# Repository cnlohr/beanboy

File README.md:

# beanboy

The beanboy is a handheld game system with 3 buttons, and an oled display.  It has the following specs:
 * Powered by a 9V Battery
 * 128x128 RB150-2828KSWKG01 SPI OLED display from Ronboe ($2.50)
 * 3 Silicone buttons with pressure sensitivity
 * TBD: Runtime
 * CH572 Main Processor
   * 240kB Flash
   * 12kB RAM
   * 60MHz
   * RISC-V rv32imbc processor
   * 2.4GHz iSLER radio comms

(Early drafts, not ready yet)

## Installation / getting started

Follow these instructions: [https://github.com/cnlohr/ch32fun/wiki](https://github.com/cnlohr/ch32fun/wiki)

## Graphics API

The bean boy uses a monochrome 128x128 display.

### Input

You get "pressures" for button 1, button 2, button 3, and the battery level. (For now, just print the values to the screen, we will be changing the levels)

```c
	uint32_t pressures[4];
	BeanBoyReadPressures( pressures );
```

### Sprites

Have .png files in `sprites/` folder, then on compile, they will turn into the object name itself, when you say `make clean firmware.elf`

```c
void RenderBSprite( const bsprite * spr, int outx, int outy );
```

For instance if you have `sprites/bubble.png`, you can call:

```c
	RenderBSprite( &bubble, x, y );
```

You can use purple or actual transparency to indicate transparent, then use white or black.

### Basic Drawing

Graphics APIs are from [the ch32v003 ssd1306 driver](https://github.com/cnlohr/ch32fun/blob/master/extralibs/ssd1306.h)

```c
#define SSD1306_W 128
#define SSD1306_H 128

void ssd1306_drawPixel(uint32_t x, uint32_t y, int color);
void ssd1306_xorPixel(uint32_t x, uint32_t y);
void ssd1306_drawImage(uint32_t x, uint32_t y, const unsigned char* input, uint32_t width, uint32_t height, uint32_t color_mode);
void ssd1306_drawFastVLine(int32_t x, int32_t y, int32_t h, uint32_t color);
void ssd1306_drawFastHLine(uint32_t x, uint32_t y, uint32_t w, uint32_t color);
void ssd1306_drawLine(int x0, int y0, int x1, int y1, uint32_t color);
void ssd1306_drawCircle(int x, int y, int radius, int color);
void ssd1306_fillCircle(int x, int y, int radius, int color);
void ssd1306_drawRect(int32_t x, int32_t y, uint32_t w, uint32_t h, uint32_t color);
void ssd1306_fillRect(uint32_t x, uint32_t y, uint8_t w, uint32_t h, uint32_t color);
void ssd1306_xorrect(uint8_t x, uint8_t y, uint8_t w, uint8_t h);
void ssd1306_drawchar(uint8_t x, uint8_t y, uint8_t chr, uint8_t color);
void ssd1306_drawstr(uint8_t x, uint8_t y, char *str, uint8_t color);
void ssd1306_drawchar_sz(uint8_t x, uint8_t y, uint8_t chr, uint8_t color, font_size_t font_size);
void ssd1306_drawstr_sz(uint8_t x, uint8_t y, char *str, uint8_t color, font_size_t font_size);
```

### Wireless API

```c
// call these
void ISLERSetup( int channel ); 
void ISLERSend( uint8_t message, int messageLength );

struct MyGameStruct
{
	uint32_t id;
	uint8_t something;
} __attribute__((packed));

void ISLERCallback( uint8_t * txmac, uint8_t * message, int messageLength, int rssi )
{
	struct MyGameStruct * st = (struct MyGameStruct*)message;

	if( messageLength < sizeof( struct MyGameStruct ) )
		return;

	printf( "%d\n", st->something );
}

void main()
{
	ISLERSetup( 9 );

	struct MyGameStruct st;
	st.id = 0x1234778a; // Some ID so you don't get confused with other BLE-messages.
	st.something = 5;

	ISLERSend( &st, sizeof( st ) );
}
```

## TODO

TODO:

1. ~~Build up two beanboys~~
2. ~~Check to see if the radio code works.~~
3. ~~Make sprite import code.~~
4. ~~Add transparency code.~~
5. ~~Add API for comms~~
6. Add networking to emu
7. Add button debouncing
8. Add compression to sprites
9. Add sprite rotation maybe?
10. Add sprite scaling maybe?
11. "Pass the puffer"  "Hot Potato with puffer fish"
  a. Choose between 2 and 6 players
  b. Randomly assign X amount of passes.
  c. number of passes remaining is unknown.
12. Shut the box.
  a. Rules too complicated for me to write here.

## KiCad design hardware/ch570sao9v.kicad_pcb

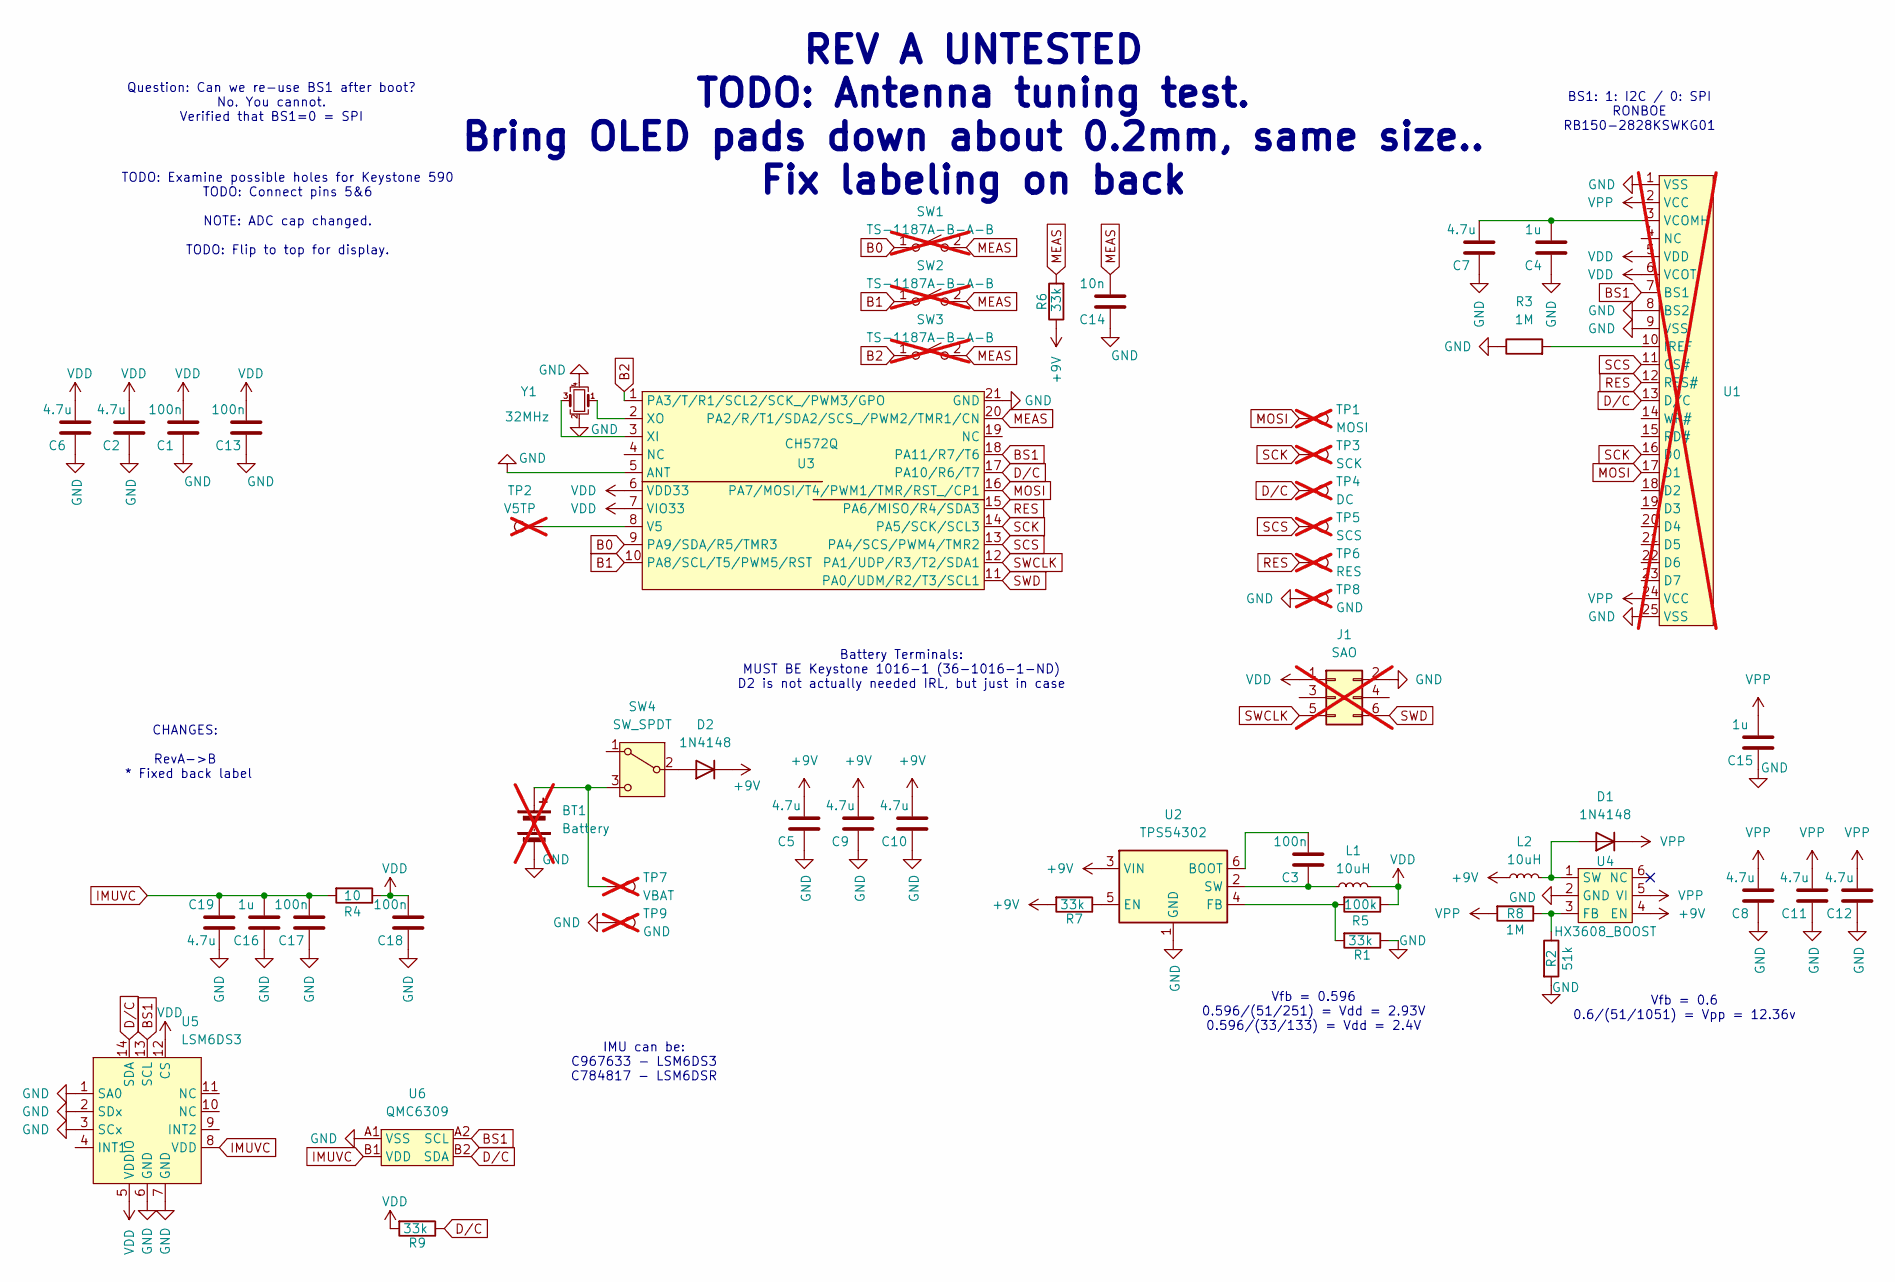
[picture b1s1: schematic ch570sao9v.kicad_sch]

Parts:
BT1: Battery; not fitted
C1, C3, C13, C17, C18: 100n; R_0402_1005Metric; LCSC C307331
C2, C5, C6, C7, C8, C9, C10, C11, C12, C19: 4.7u; C_1206_3216Metric; LCSC C29823
C4, C15, C16: 1u; R_0402_1005Metric; LCSC C52923
C14: 10n; R_0402_1005Metric; LCSC C15195
D1, D2: 1N4148; D_SOD-323; LCSC C2128
J1: SAO; PinHeader_2x03_P2.54mm_Vertical_SMD; not fitted
L1, L2: 10uH; L_1008_2520Metric; LCSC C37428
R1, R6, R7, R9: 33k; R_0402_1005Metric_COMPACT; LCSC C25779
R2: 51k; R_0402_1005Metric_COMPACT; LCSC C25794
R3, R8: 1M; R_0402_1005Metric_COMPACT; LCSC C26083
R4: 10; R_0402_1005Metric_COMPACT; LCSC C25077
R5: 100k; R_0402_1005Metric_COMPACT; LCSC C25741
SW1, SW2, SW3: TS-1187A-B-A-B; BTC007_Button_Silicone; not fitted
SW4: SW_SPDT; SW_SPDT_PCM12; LCSC C3008585
TP1: MOSI; TestPoint_Pad_D1.0mm; not fitted
TP2: V5TP; TestPoint_Pad_D1.0mm; not fitted
TP3: SCK; TestPoint_Pad_D1.0mm; not fitted
TP4: DC; TestPoint_Pad_D1.0mm; not fitted
TP5: SCS; TestPoint_Pad_D1.0mm; not fitted
TP6: RES; TestPoint_Pad_D1.0mm; not fitted
TP7: VBAT; TestPoint_Pad_D1.0mm; LCSC C6063943; not fitted
TP8: GND; TestPoint_Pad_D1.0mm; not fitted
TP9: GND; TestPoint_Pad_D1.0mm; LCSC C6063943; not fitted
U1: RB150-2828KSWKG01; not fitted
U2: TPS54302; SOT-23-6; LCSC C311983
U3: CH572Q; QFN-20-1EP_3x3mm_P0.4mm_EP1.65x1.65mm; LCSC C46597863
U4: HX3608_BOOST; SOT-23-6; LCSC C296278
U5: LSM6DS3; LGA-14_3x2.5mm_P0.5mm_LayoutBorder3x4y_EVEN_PADS; LCSC C784817
U6: QMC6309; WLP-4_0.83x0.83mm_P0.4mm; LCSC C5439871
Y1: 32MHz; Crystal_SMD_2016-4Pin_2.0x1.6mm; LCSC C37635323

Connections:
+9V: C5.1, C9.1, C10.1, D2.1 (K), L2.1, R6.1, R7.2, U2.3 (VIN), U4.4 (EN)
B0: SW1.1 (A), U3.9 (PA9/SDA/R5/TMR3)
B1: SW2.1 (A), U3.10 (PA8/SCL/T5/PWM5/RST)
B2: SW3.1 (A), U3.1 (PA3/T/R1/SCL2/SCK_/PWM3/GPO)
BS1: U1.7 (BS1), U3.18 (PA11/R7/T6), U5.13 (SCL), U6.A2 (SCL)
D/C: R9.1, TP4.1, U1.13 (D/C), U3.17 (PA10/R6/T7), U5.14 (SDA), U6.B2 (SDA)
GND: BT1.2 (-), C1.2, C2.2, C4.2, C5.2, C6.2, C7.2, C8.2, C9.2, C10.2, C11.2, C12.2, C13.2, C14.2, C15.2, C16.2, C17.2, C18.2, C19.1, J1.2, R1.1, R2.2, R3.1, TP8.1, TP9.1, U1.1 (VSS), U1.8 (BS2), U1.9 (VSS), U1.25 (VSS), U2.1 (GND), U3.5 (ANT), U3.21 (GND), U4.2 (GND), U5.1 (SA0), U5.2 (SDx), U5.3 (SCx), U5.6 (GND), U5.7 (GND), U6.A1 (VSS), Y1.2, Y1.4
IMUVC: C16.1, C17.1, C19.2, R4.2, U5.8 (VDD), U6.B1 (VDD)
MEAS: C14.1, R6.2, SW1.2 (B), SW2.2 (B), SW3.2 (B), U3.20 (PA2/R/T1/SDA2/SCS_/PWM2/TMR1/CN)
MOSI: TP1.1, U1.17 (D1), U3.16 (PA7/MOSI/T4/PWM1/TMR/RST_/CP1)
unnamed: BT1.1 (+), SW4.3 (C), TP7.1
unnamed: D1.2 (A), L2.2, U4.1 (SW)
unnamed: D2.2 (A), SW4.2 (B)
unnamed: R3.2, U1.10 (IREF)
unnamed: C4.1, C7.1, U1.3 (VCOMH)
unnamed: C3.1, U2.6 (BOOT)
unnamed: R7.1, U2.5 (EN)
unnamed: R1.2, R5.2, U2.4 (FB)
unnamed: C3.2, L1.1, U2.2 (SW)
unnamed: TP2.1, U3.8 (V5)
unnamed: U3.3 (XI), Y1.3
unnamed: U3.2 (XO), Y1.1
unnamed: R2.1, R8.1, U4.3 (FB)
RES: TP6.1, U1.12 (RES#), U3.15 (PA6/MISO/R4/SDA3)
SCK: TP3.1, U1.16 (D0), U3.14 (PA5/SCK/SCL3)
SCS: TP5.1, U1.11 (CS#), U3.13 (PA4/SCS/PWM4/TMR2)
SWCLK: J1.5, U3.12 (PA1/UDP/R3/T2/SDA1)
SWD: J1.6, U3.11 (PA0/UDM/R2/T3/SCL1)
VDD: C1.1, C2.1, C6.1, C13.1, C18.1, J1.1, L1.2, R4.1, R5.1, R9.2, U1.5 (VDD), U1.6 (VCOT), U3.6 (VDD33), U3.7 (VIO33), U5.5 (VDDIO), U5.12 (CS)
VPP: C8.1, C11.1, C12.1, C15.1, D1.1 (K), R8.2, U1.2 (VCC), U1.24 (VCC), U4.5 (VI)

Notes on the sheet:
REV A UNTESTED TODO: Antenna tuning test. Bring OLED pads down about 0.2mm, same size.. Fix labeling on back
TODO: Examine possible holes for Keystone 590 TODO: Connect pins 5&6 NOTE: ADC cap changed. TODO: Flip to top for display.
Question: Can we re-use BS1 after boot? No. You cannot. Verified that BS1=0 = SPI
IMU can be: C967633 - LSM6DS3 C784817 - LSM6DSR
Vfb = 0.596 0.596/(51/251) = Vdd = 2.93V 0.596/(33/133) = Vdd = 2.4V
Vfb = 0.6 0.6/(51/1051) = Vpp = 12.36v
CHANGES: RevA->B * Fixed back label
Battery Terminals: MUST BE Keystone 1016-1 (36-1016-1-ND) D2 is not actually needed IRL, but just in case
BS1: 1: I2C / 0: SPI RONBOE RB150-2828KSWKG01

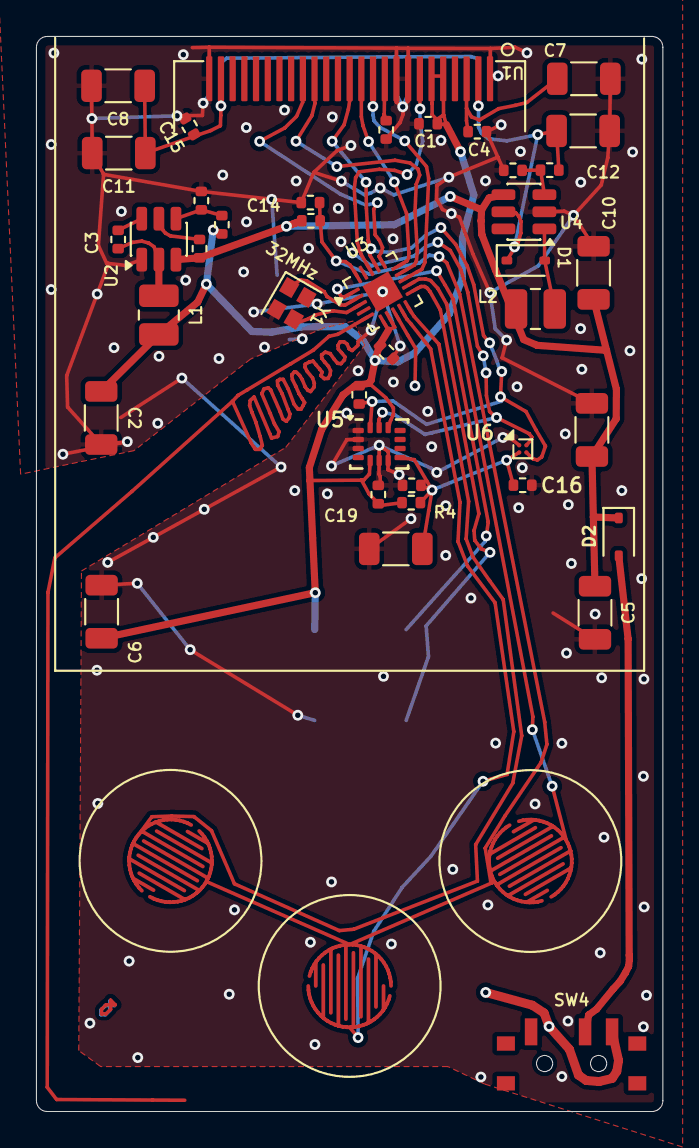
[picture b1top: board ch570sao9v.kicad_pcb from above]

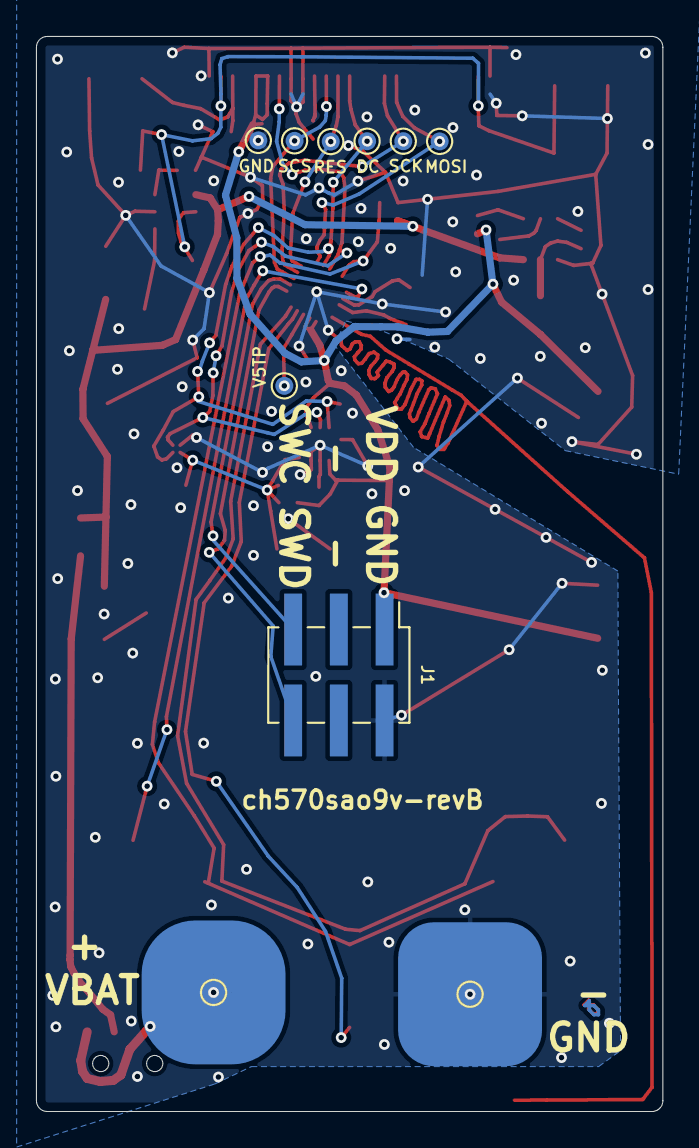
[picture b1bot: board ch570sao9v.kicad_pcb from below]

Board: 2 copper layers, 34.8 x 59.7 mm, 53 parts (10 on the bottom side), 30 nets.

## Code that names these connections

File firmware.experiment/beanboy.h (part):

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{
	R8_TMR_INT_FLAG = 2;
	lastfifo = R32_TMR_FIFO;
	funPinMode( PA2, GPIO_ModeOut_PP_20mA );
}


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{
	R8_TMR_CTRL_MOD = 0b00000010; // Reset Timer
	R8_TMR_CTRL_MOD = 0b11000101; // Capture mode rising edge
	funPinMode( PA2, GPIO_ModeIN_Floating );
}

static void SetupADC(void)
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	R8_TMR_CTRL_MOD = 0b11000101; // Capture mode rising edge
	R8_TMR_INTER_EN = 0b10; // Capture event.

	R16_PIN_ALTERNATE_H |= 1<<6; // Map PA2 to CAP1 (could be PA7, PA4, or PA9) (see RB_TMR_PIN)

	NVIC_EnableIRQ(TMR1_IRQn);
	__enable_irq();

	funPinMode( PA2, GPIO_ModeOut_PP_20mA );
}

static void BeanBoyReadPressures( uint32_t * pressures )
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	for( btn = 0; btn < 4; btn++ )
	{
		// try GPIO_CFGLR_IN_PUPD, GPIO_ModeIN_Floating, GPIO_CFGLR_OUT_10Mhz_PP as well
		funPinMode( PA3, GPIO_ModeIN_Floating );
		funPinMode( PA8, GPIO_ModeIN_Floating );
		funPinMode( PA9, GPIO_ModeIN_Floating );
		switch( btn )
		{
		case 0:
			funPinMode( PA8, GPIO_CFGLR_OUT_10Mhz_PP );
			funDigitalWrite( PA3, 1 );
			break;
		case 1:
			funPinMode( PA9, GPIO_CFGLR_OUT_10Mhz_PP );
			funDigitalWrite( PA8, 1 );
			break;
		case 2:
			funPinMode( PA3, GPIO_CFGLR_OUT_10Mhz_PP );
			funDigitalWrite( PA9, 1 );
			break;
		}

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/////////////////////////////////////////////////////////////////////////////////////////////////


#define PIN_SDA PA10
#define PIN_SCL PA11

#define DELAY1 ADD_N_NOPS(20) // Delay_Us(1);
#define DELAY2 ADD_N_NOPS(30) // Delay_Us(1);
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
	funPinMode( PIN_SCL, GPIO_CFGLR_OUT_2Mhz_PP );
	funPinMode( PIN_SDA, GPIO_CFGLR_OUT_2Mhz_PP );
	funDigitalWrite( PA11, 0 ); // BS1 = 0 for SPI
	funDigitalWrite( PA10, 1 ); // D/C
}

void DoI2C()
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
	funPinMode( PIN_SCL, GPIO_CFGLR_OUT_2Mhz_PP );
	funPinMode( PIN_SDA, GPIO_CFGLR_OUT_2Mhz_PP );
	funDigitalWrite( PA11, 0 ); // BS1 = 0 for SPI
	funDigitalWrite( PA10, 1 ); // D/C
}

/////////////////////////////////////////////////////////////////////////////////////////////////
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
	funGpioInitAll(); // no-op on ch5xx

	funPinMode( PA11, GPIO_CFGLR_OUT_10Mhz_PP );
//	funDigitalWrite( PA11, 1 ); // BS1 = 1 for I2C
	funDigitalWrite( PA11, 0 ); // BS1 = 0 for SPI

	funPinMode( PA6, GPIO_CFGLR_OUT_10Mhz_PP );
	funDigitalWrite( PA6, 1 ); // RES
	funPinMode( PA4, GPIO_CFGLR_OUT_10Mhz_PP );
	funDigitalWrite( PA4, 0 ); // SCS
	funPinMode( PA10, GPIO_CFGLR_OUT_10Mhz_PP );
	funDigitalWrite( PA10, 0 ); // D/C

	SetupI2C();

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
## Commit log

2025-12-07 Add skeleton project
2025-12-07 Update design
2025-12-11 Update to rev a
2025-12-12 Update rev a
2025-12-19 Update readme, firmware.
2025-12-19 Add asset rendering
2025-12-19 Add bubble
2025-12-19 Update emu to work with new build
2025-12-19 Update with testing both types of transparency.
2025-12-19 Update notes
2025-12-19 Add workflow
2025-12-19 Tweak build
2025-12-19 Updat CI, readme tweak + fix linguist languages
2025-12-19 Add makeassets
2025-12-19 Update with gitattrbitues
2025-12-19 Fixup ci
2025-12-19 Bump
2025-12-19 Add need for networking to emu
2025-12-25 Bump design
2025-12-26 Fix code
2025-12-26 Update firmware with I2C stuff
2025-12-26 Bump code
2025-12-26 Add bean boy rev B
2025-12-29 ADd experimental firmware
2025-12-30 bump submodule
2025-12-30 bump with game mode
2025-12-30 Add example
2025-12-30 test commit
2025-12-30 catching up to main
2025-12-30 Clean install merge
2025-12-30 Add game pointer
2025-12-30 Fix bug
2025-12-30 1. Update my stuff 2. Fix delta time
2025-12-30 Fix time base
2025-12-30 Update submodule
2025-12-30 small commit
2025-12-30 Getting close to something working.
2025-12-31 Update emu with randomness and fix error
2025-12-31 add entropy
2025-12-31 Improve entropy
2025-12-31 It's a game! Mostly!
2025-12-31 Update system to enable wireless comms
2025-12-31 Make radio comms shoddy
2026-01-02 Art Problems
2026-01-02 small test commit
2026-01-02 Update ch32fun submodule
2026-01-02 Bump with the start of a sin() function
2026-01-02 Functional Shippable Game
2026-01-03 Mode working well, art to follow
2026-01-03 Polished up, looking smooth
2026-01-03 Working with bean
2026-01-03 Got something pretty baller.
2026-01-04 Working IMU math
2026-01-04 Getting very close to done
2026-01-04 Oope switch menu back + I think my mode is done
2026-01-04 few more tweaks
2026-01-04 Further tweaks
2026-01-04 * Fix graphics performance * Make IMU work for example apps
2026-01-04 Remove extra printf
2026-01-04 Add Reboot() function
2026-01-04 Make timing and add pause feature.
2026-01-04 Prepare for more artwork
2026-01-04 Fixup some bugs in the IMU code and improve performance
2026-01-04 A few more tweaks.
2026-01-05 Small changes to mirror main
2026-01-05 Stashing changes, ready for animations
2026-01-05 Add donut to models
2026-01-05 Add donut
2026-01-05 Groundwork laid for blackjack
2026-01-05 Update mode test with teapot
2026-01-05 Update obj2file
2026-01-05 Remove firmware.bin from committed artifacts
2026-01-05 Meake main menu neater + update my test mode
2026-01-05 fix warning
2026-01-05 Fix bunny vertex ADd back in crash handler
2026-01-05 Dunno why but resetting caused issues for the OLED
2026-01-06 Small push
2026-01-07 Pushing 3d Files
2026-01-07 Added Death Animation
2026-01-07 Puffer: Passed
2026-01-07 Mac Compatibility
2026-01-07 compiled all assets
2026-01-07 Maybe works?
2026-01-07 remove firmware.bin remove isler
2026-01-07 Ready to fix shutbox
2026-01-07 Improved shut the box and gitignore
2026-01-07 Removed puffer blinking rect
2026-01-07 Fix test
2026-01-07 Fix mode menu - don't overwrite data
2026-01-07 Update with aquarium mode
2026-01-07 Bubbles!
2026-01-15 Remove firmware.experiment, and update design
